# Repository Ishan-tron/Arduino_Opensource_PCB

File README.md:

# Arduino_Opensource_PCB
Arduino PCB Designs on KICAD

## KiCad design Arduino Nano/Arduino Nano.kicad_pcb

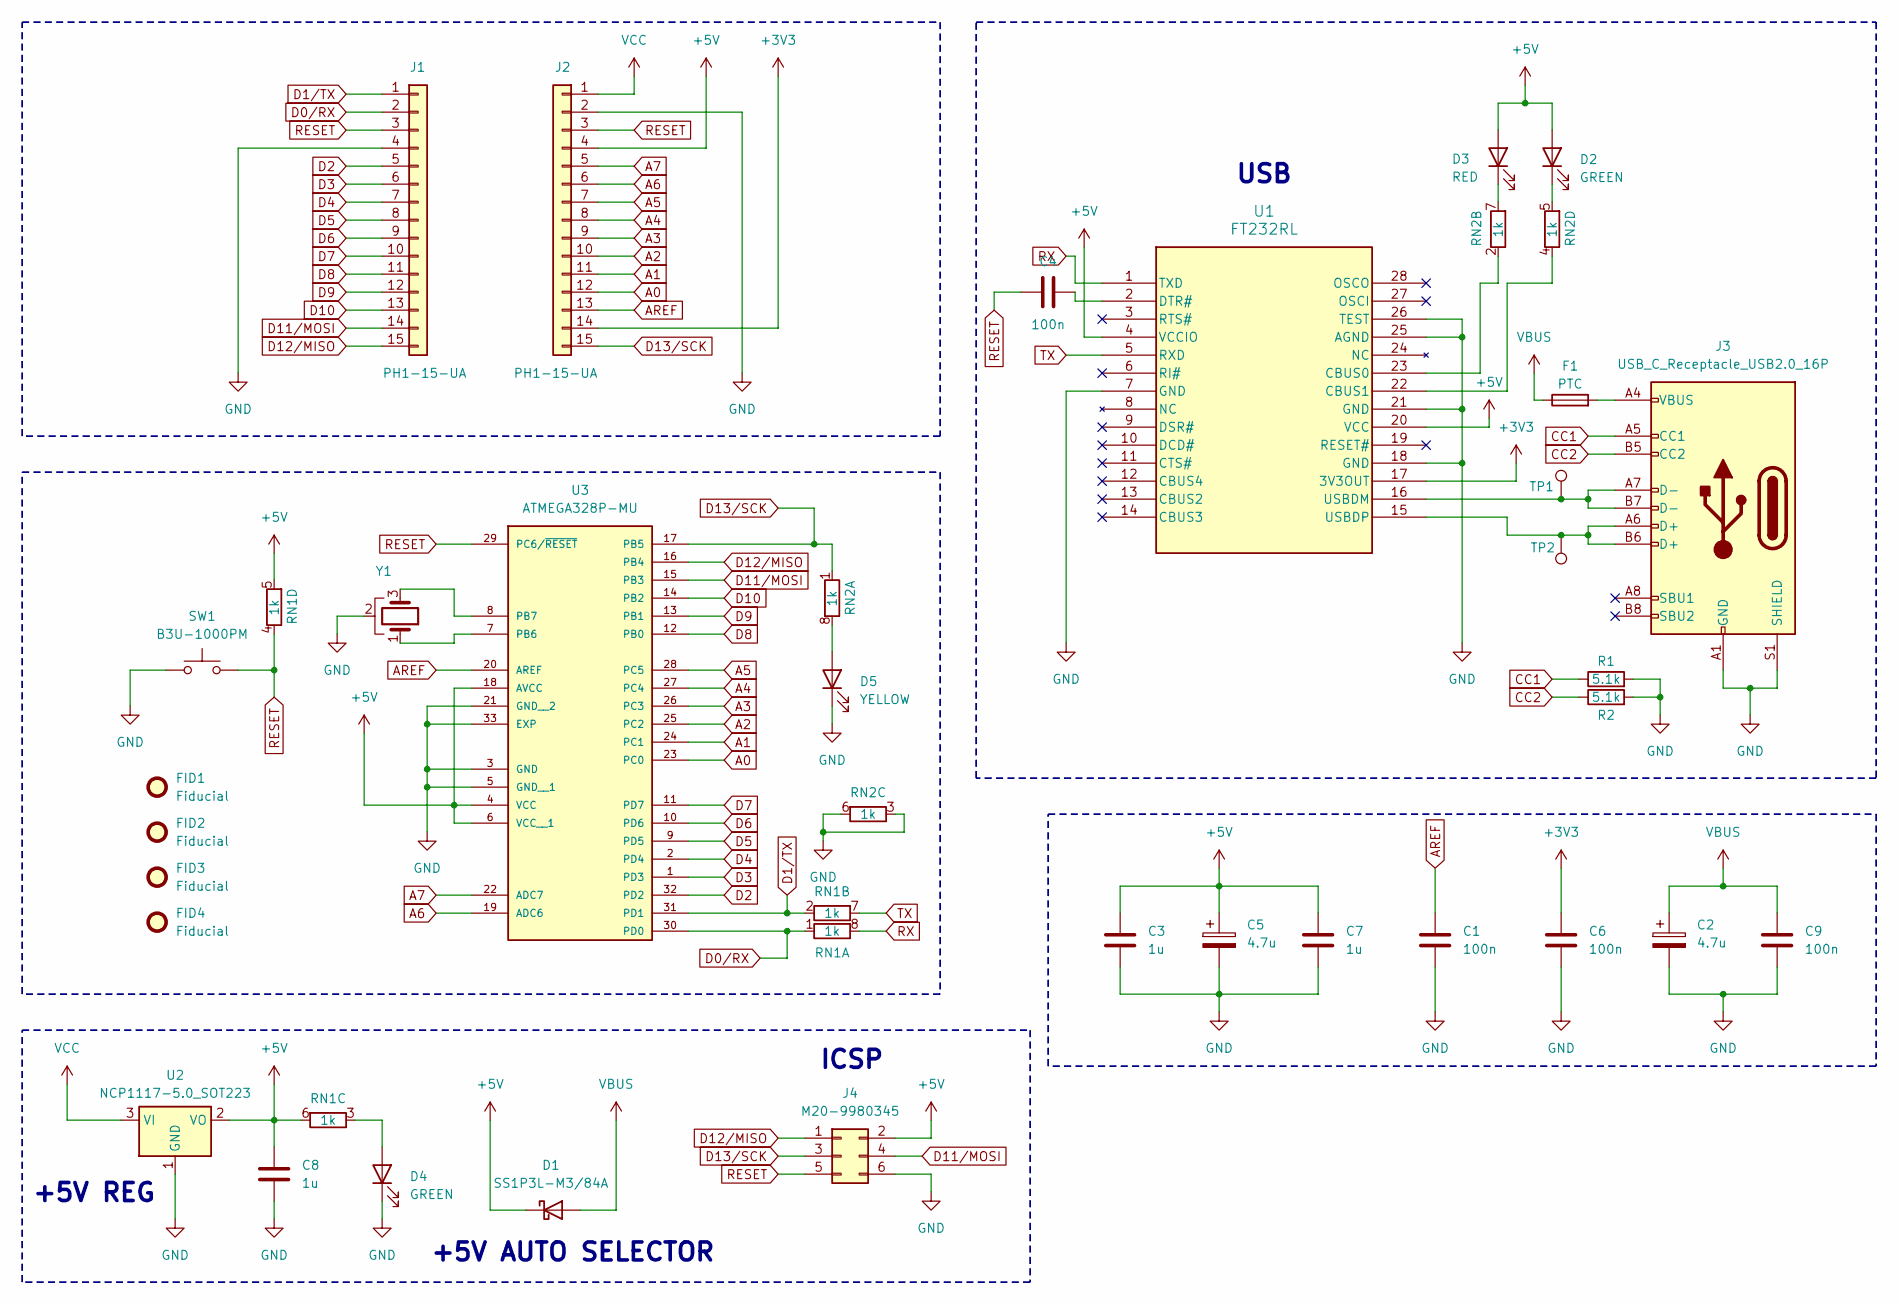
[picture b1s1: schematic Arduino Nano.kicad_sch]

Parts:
C1, C4, C6, C9: 100n; C_0603_1608Metric
C2, C5: 4.7u; CP_EIA-3216-10_Kemet-I
C3, C7, C8: 1u; C_0603_1608Metric
D1: SS1P3L-M3/84A; D_SMP_DO-220AA
D2, D4: GREEN; LED_0805_2012Metric
D3: RED; LED_0805_2012Metric
D5: YELLOW; LED_0805_2012Metric
F1: PTC; Fuse_0603_1608Metric
FID1, FID2, FID3, FID4: Fiducial; Fiducial_1mm_Mask2mm
J1, J2: PH1-15-UA; PinHeader_1x15_P2.54mm_Vertical
J3: USB_C_Receptacle_USB2.0_16P; USB_C_Receptacle_GCT_USB4110
J4: M20-9980345; PinHeader_2x03_P2.54mm_Vertical
R1, R2: 5.1k; R_0603_1608Metric
RN1, RN2: 1k; R_Array_Convex_4x0612
SW1: B3U-1000PM
TP1, TP2: TestPoint; TestPoint_Pad_D1.0mm
U1: FT232RL; SSOP-28_5.3x10.2mm_P0.65mm
U2: NCP1117-5.0_SOT223; SOT-223-3_TabPin2
U3: ATMEGA328P-MU; VQFN-32-1EP_5x5mm_P0.5mm_EP3.1x3.1mm
Y1: CSTNE16M0V530000R0; Resonator_SMD_Murata_CSTxExxV-3Pin_3.0x1.1mm

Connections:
+3V3: C6.2, J2.14, U1.17 (3V3OUT)
+5V: C3.1, C5.1, C7.1, C8.1, D1.1 (K), D2.2 (A), D3.2 (A), J2.4, J4.2, RN1.5 (R4.2), RN1.6 (R3.2), U1.4 (VCCIO), U1.20 (VCC), U2.2 (VO), U3.4 (VCC), U3.6 (VCC__1), U3.18 (AVCC)
A0: J2.12, U3.23 (PC0)
A1: J2.11, U3.24 (PC1)
A2: J2.10, U3.25 (PC2)
A3: J2.9, U3.26 (PC3)
A4: J2.8, U3.27 (PC4)
A5: J2.7, U3.28 (PC5)
A6: J2.6, U3.19 (ADC6)
A7: J2.5, U3.22 (ADC7)
AREF: C1.1, J2.13, U3.20 (AREF)
CC1: J3.A5 (CC1), R1.1
CC2: J3.B5 (CC2), R2.1
D0/RX: J1.2, RN1.1 (R1.1), U3.30 (PD0)
D1/TX: J1.1, RN1.2 (R2.1), U3.31 (PD1)
D2: J1.5, U3.32 (PD2)
D3: J1.6, U3.1 (PD3)
D4: J1.7, U3.2 (PD4)
D5: J1.8, U3.9 (PD5)
D6: J1.9, U3.10 (PD6)
D7: J1.10, U3.11 (PD7)
D8: J1.11, U3.12 (PB0)
D9: J1.12, U3.13 (PB1)
D10: J1.13, U3.14 (PB2)
D11/MOSI: J1.14, J4.4, U3.15 (PB3)
D12/MISO: J1.15, J4.1, U3.16 (PB4)
D13/SCK: J2.15, J4.3, RN2.1 (R1.1), U3.17 (PB5)
GND: C1.2, C2.2, C3.2, C5.2, C6.1, C7.2, C8.2, C9.2, D4.1 (K), D5.1 (K), J1.4, J2.2, J3.A1 (GND), J3.A12 (GND), J3.B1 (GND), J3.B12 (GND), J3.S1 (SHIELD), J4.6, R1.2, R2.2, RN2.3 (R3.1), RN2.6 (R3.2), SW1.1, U1.7 (GND), U1.18 (GND), U1.21 (GND), U1.25 (AGND), U1.26 (TEST), U2.1 (GND), U3.3 (GND), U3.5 (GND__1), U3.21 (GND__2), U3.33 (EXP), Y1.2
unnamed: D2.1 (K), RN2.5 (R4.2)
unnamed: D3.1 (K), RN2.7 (R2.2)
unnamed: D4.2 (A), RN1.3 (R3.1)
unnamed: D5.2 (A), RN2.8 (R1.2)
unnamed: F1.2, J3.A4 (VBUS), J3.A9 (VBUS), J3.B4 (VBUS), J3.B9 (VBUS)
unnamed: RN2.2 (R2.1), U1.23 (CBUS0)
unnamed: RN2.4 (R4.1), U1.22 (CBUS1)
unnamed: C4.2, U1.2 (DTR#)
unnamed: J3.A7 (D-), J3.B7 (D-), TP1.1, U1.16 (USBDM)
unnamed: J3.A6 (D+), J3.B6 (D+), TP2.1, U1.15 (USBDP)
unnamed: U3.7 (PB6), Y1.1
unnamed: U3.8 (PB7), Y1.3
RESET: C4.1, J1.3, J2.3, J4.5, RN1.4 (R4.1), SW1.2, U3.29 (PC6/~RESET)
RX: RN1.8 (R1.2), U1.1 (TXD)
TX: RN1.7 (R2.2), U1.5 (RXD)
VBUS: C2.1, C9.1, D1.2 (A), F1.1
VCC: J2.1, U2.3 (VI)

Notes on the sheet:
ICSP
USB
+5V AUTO SELECTOR
+5V REG

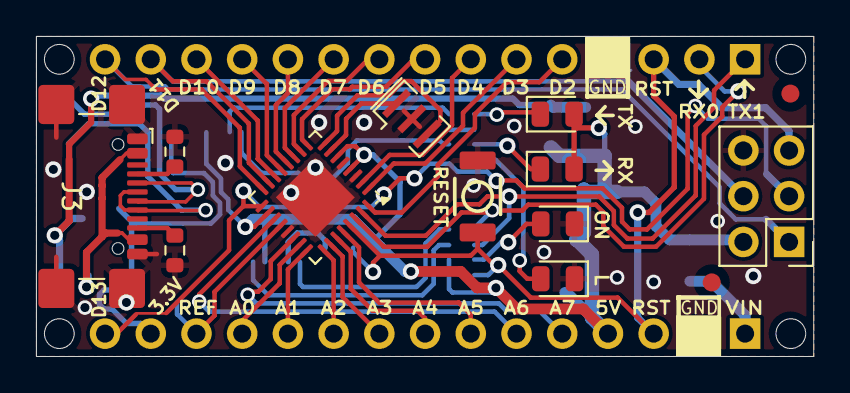
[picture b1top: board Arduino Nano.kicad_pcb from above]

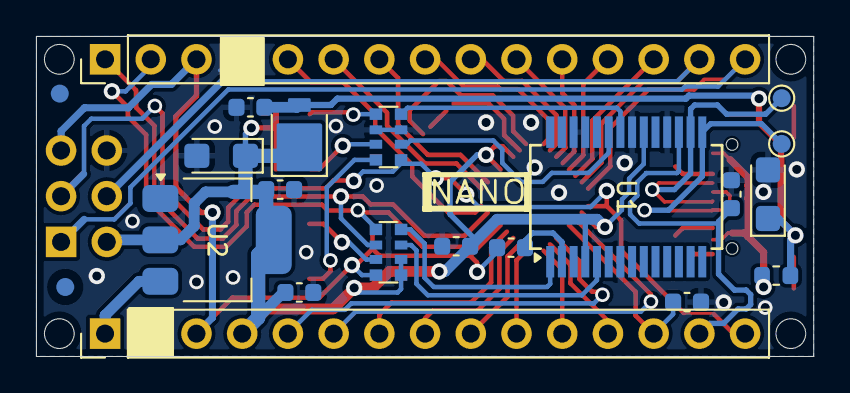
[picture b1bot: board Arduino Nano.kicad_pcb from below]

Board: 2 copper layers, 43.2 x 17.8 mm, 34 parts (21 on the bottom side), 45 nets.

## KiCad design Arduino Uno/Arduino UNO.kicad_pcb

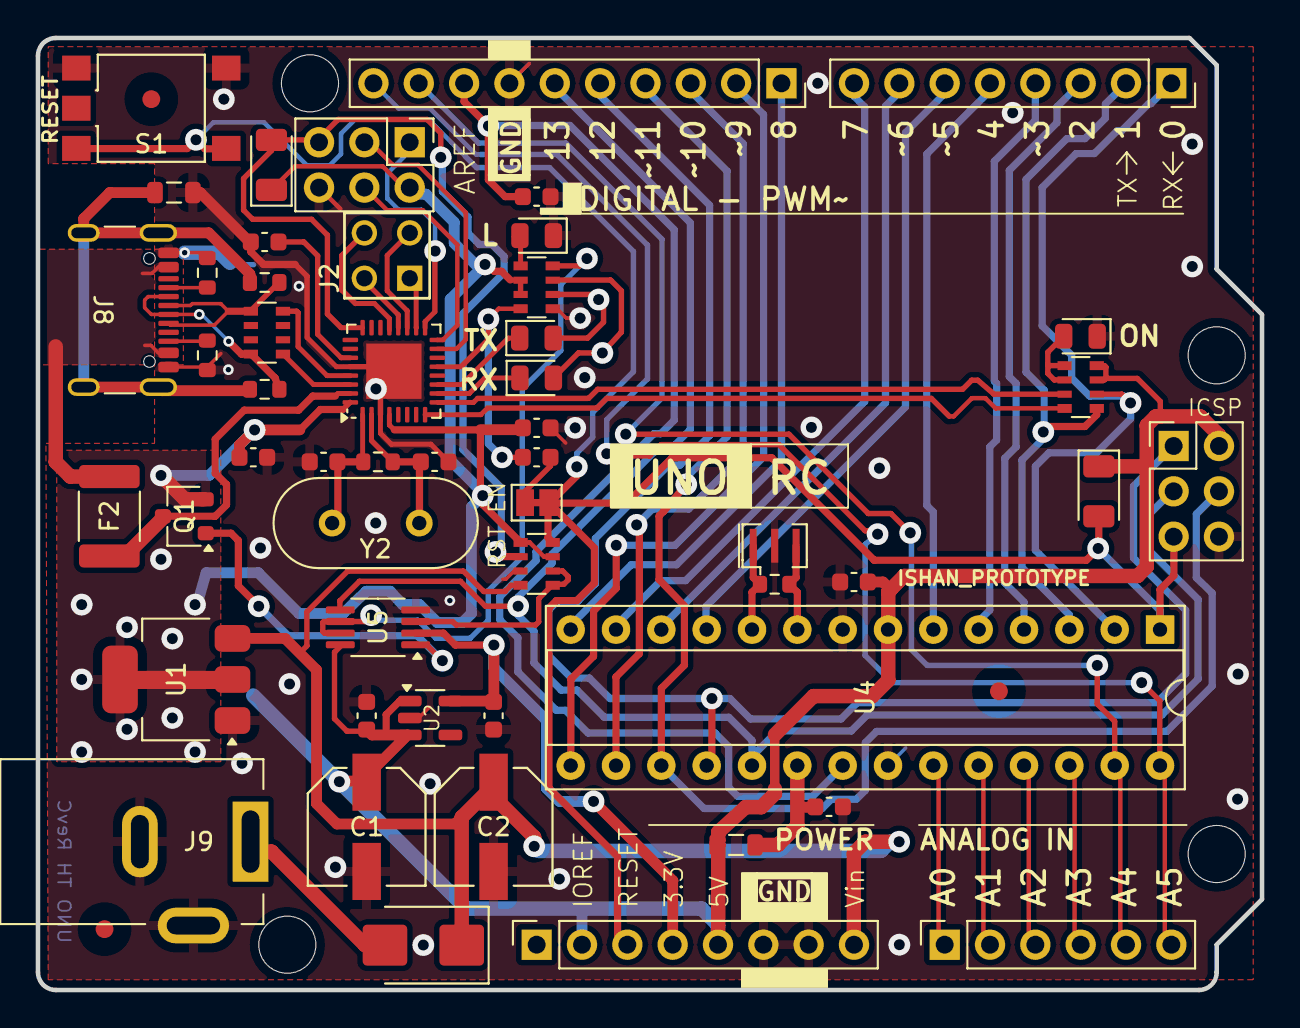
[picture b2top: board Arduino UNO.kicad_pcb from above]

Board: 2 copper layers, 68.6 x 53.3 mm, 56 parts (1 on the bottom side), 62 nets.

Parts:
C1, C2: 47u; CAP_EEHZA1E470P
C3, C4, C6, C7, C8, C9, C12: 100n; C_0603_1608Metric
C5, C10: 1u; C_0603_1608Metric
C11, C13: 22p; C_0603_1608Metric
D1: CGRB307-G; D_SMB
D2, D3: CD1206-S01575; D_1206_3216Metric
D4, D5, D6: YELLOW; LED_0805_2012Metric
D7: GREEN; LED_0805_2012Metric
F2: MF-MSMF050-2; Fuse_1812_4532Metric_Pad1.30x3.40mm_HandSolder
FB1: 1kΩ@100MHz; L_0805_2012Metric
FB2: 10uH; L_0805_2012Metric
FID1, FID2, FID3: Fiducial; Fiducial_1mm_Mask3mm
J1, J3: M20-9980345; PinHeader_2x03_P2.54mm_Vertical
J2: M20-9980245; CONN_M20-9980245_HRW
J4: PPTC101LFBN-RC; PinSocket_1x10_P2.54mm_Vertical
J5, J7: PPTC081LFBN-RC; PinSocket_1x08_P2.54mm_Vertical
J6: PPTC061LFBN-RC; PinSocket_1x06_P2.54mm_Vertical
J8: USB_C_Receptacle_USB2.0_16P; USB_C_Receptacle_GCT_USB4105-xx-A_16P_TopMnt_Horizontal
J9: PJ-102AH; BarrelJack_Kycon_KLDX-0202-xC_Horizontal
JP1, JP2: SolderJumper_2_Open; SolderJumper-2_P1.3mm_Open_Pad1.0x1.5mm
Q1: FDN340P; SC-59
R1, R2: 1M; R_0603_1608Metric
R3, R4: 5k1; R_0603_1608Metric
RN1: 10k; R_Array_Convex_4x0603
RN2, RN4: 1k; R_Array_Convex_4x0603
RN3: 22R; R_Array_Convex_4x0603
S1: TS06-667-30-BK-100-G-SMT-TR; SW_TS06-667-30-BK-100-G-SMT-TR
U1: NCP1117-5.0_SOT223; SOT-223-3_TabPin2
U2: LP2985-3.3; SOT-23-5
U3: ATMEGA16U2-MU; VQFN-32-1EP_5x5mm_P0.5mm_EP3.1x3.1mm
U4: ATMEGA328P-PU; DIP-28_W7.62mm_Socket
U5: LMV358IDGKR; MSOP-8_3x3mm_P0.65mm
Y1: CSTNE16M0V530000R0; Resonator_SMD_Murata_CSTxExxV-3Pin_3.0x1.1mm
Y2: LFXTAL003240BULK; Crystal_HC49-4H_Vertical
Z1, Z2: 5pF@1MHz; R_0603_1608Metric

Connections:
+3.3V: C5.2, J7.4, U2.5 (VOUT), U5.2
+5V: C1.1, C3.2, C4.1, C8.2, C9.1, D2.1 (K), D3.1 (K), FB2.1, J1.2, J3.2, J7.2, J7.5, Q1.2 (S), RN1.3 (R3.1), RN1.5 (R4.2), RN2.2 (R2.1), RN2.3 (R3.1), RN4.3 (R3.1), RN4.4 (R4.1), U1.2 (VO), U2.1 (VIN), U2.3 (ON/~OFF), U3.4 (VCC), U3.32 (AVCC), U4.7 (VCC), U5.8 (VCC+)
AD0: J6.1, U4.23 (PC0)
AD1: J6.2, U4.24 (PC1)
AD2: J6.3, U4.25 (PC2)
AD3: J6.4, U4.26 (PC3)
AD4/SDA: J4.9, J6.5, U4.27 (PC4)
AD5/SCL: J4.10, J6.6, U4.28 (PC5)
AREF: C6.1, J4.8, U4.21 (AREF)
AVCC: C12.1, FB2.2, U4.20 (AVCC)
CC1: J8.A5 (CC1), R3.1
CC2: J8.B5 (CC2), R4.1
CMP: RN1.1 (R1.1), RN1.2 (R2.1), U5.3
D+: J8.A6 (D+), J8.B6 (D+), RN3.5 (R4.2), Z1.1
D-: J8.A7 (D-), J8.B7 (D-), RN3.8 (R1.2), Z2.1
DTR: C7.1, RN2.4 (R4.1), U3.13 (PD7)
GATE_CMD: Q1.1 (G), U5.1
GND: C1.2, C2.2, C3.1, C4.2, C5.1, C6.2, C8.1, C9.2, C10.1, C11.2, C12.2, C13.2, D4.1 (K), D7.1 (K), FB1.2, J1.6, J3.6, J4.7, J7.6, J7.7, J8.A1 (GND), J8.A12 (GND), J8.B1 (GND), J8.B12 (GND), J9.2, J9.3, JP2.1 (A), JP2.2 (B), R3.2, R4.2, RN1.7 (R2.2), RN2.5 (R4.2), S1.1, S1.2, U1.1 (GND), U2.2 (GND), U3.3 (GND), U3.28 (UGND), U3.33 (EXP), U4.8 (GND), U4.22 (GND__1), U5.4 (GND), Y1.2
IO0: J5.1, RN4.2 (R2.1), U4.2 (PD0)
IO1: J5.2, RN4.1 (R1.1), U4.3 (PD1)
IO2: J5.3, U4.4 (PD2)
IO3: J5.4, U4.5 (PD3)
IO4: J5.5, U4.6 (PD4)
IO5: J5.6, U4.11 (PD5)
IO6: J5.7, U4.12 (PD6)
IO7: J5.8, U4.13 (PD7)
IO8: J4.1, U4.14 (PB0)
IO9: J4.2, U4.15 (PB1)
M8RXD: RN4.7 (R2.2), U3.9 (PD3)
M8TXD: RN4.8 (R1.2), U3.8 (PD2)
MISO: J3.1, J4.5, U4.18 (PB4)
MISO2: J1.1, U3.17 (PB3)
MOSI: J3.4, J4.4, U4.17 (PB3)
MOSI2: J1.4, U3.16 (PB2)
unnamed: D1.2 (A), J9.1
unnamed: D4.2 (A), RN2.1 (R1.1)
unnamed: D5.2 (A), RN2.6 (R3.2)
unnamed: D6.2 (A), RN2.7 (R2.2)
unnamed: D7.2 (A), RN4.5 (R4.2), RN4.6 (R3.2)
unnamed: RN2.8 (R1.2), U5.6, U5.7
unnamed: C13.1, R1.1, U3.2 (PC0), Y2.1
unnamed: C10.2, U3.27 (UCAP)
unnamed: C11.1, R1.2, U3.1 (XTAL1), Y2.2
unnamed: R2.2, U4.9 (PB6), Y1.3
unnamed: R2.1, U4.10 (PB7), Y1.1
PB4: J2.1, U3.18 (PB4)
PB5: J2.3, U3.19 (PB5)
PB6: J2.2, U3.20 (PB6)
PB7: J2.4, U3.21 (PB7)
RD+: RN3.4 (R4.1), U3.29 (D+)
RD-: RN3.1 (R1.1), U3.30 (D-)
RESET: C7.2, D2.2 (A), J3.5, J7.3, JP1.1 (A), JP1.2 (B), RN1.4 (R4.1), S1.3, S1.4, U4.1 (PC6/~RESET)
RESET2: D3.2 (A), J1.5, RN1.6 (R3.2), U3.24 (PC1//~RESET)
RXLED: D6.1 (K), U3.10 (PD4)
SCK: J3.3, J4.6, U4.19 (PB5), U5.5
SCK2: J1.3, U3.15 (PB1)
SS: J4.3, U4.16 (PB2)
TXLED: D5.1 (K), U3.11 (PD5)
USBVCC: F2.2, Q1.3 (D), U3.31 (UVCC)
USHIELD: FB1.1, J8.S1 (SHIELD), Z1.2, Z2.2
VCC: C2.1, D1.1 (K), J7.8, RN1.8 (R1.2), U1.3 (VI)
XUSB: F2.1, J8.A4 (VBUS), J8.A9 (VBUS), J8.B4 (VBUS), J8.B9 (VBUS)

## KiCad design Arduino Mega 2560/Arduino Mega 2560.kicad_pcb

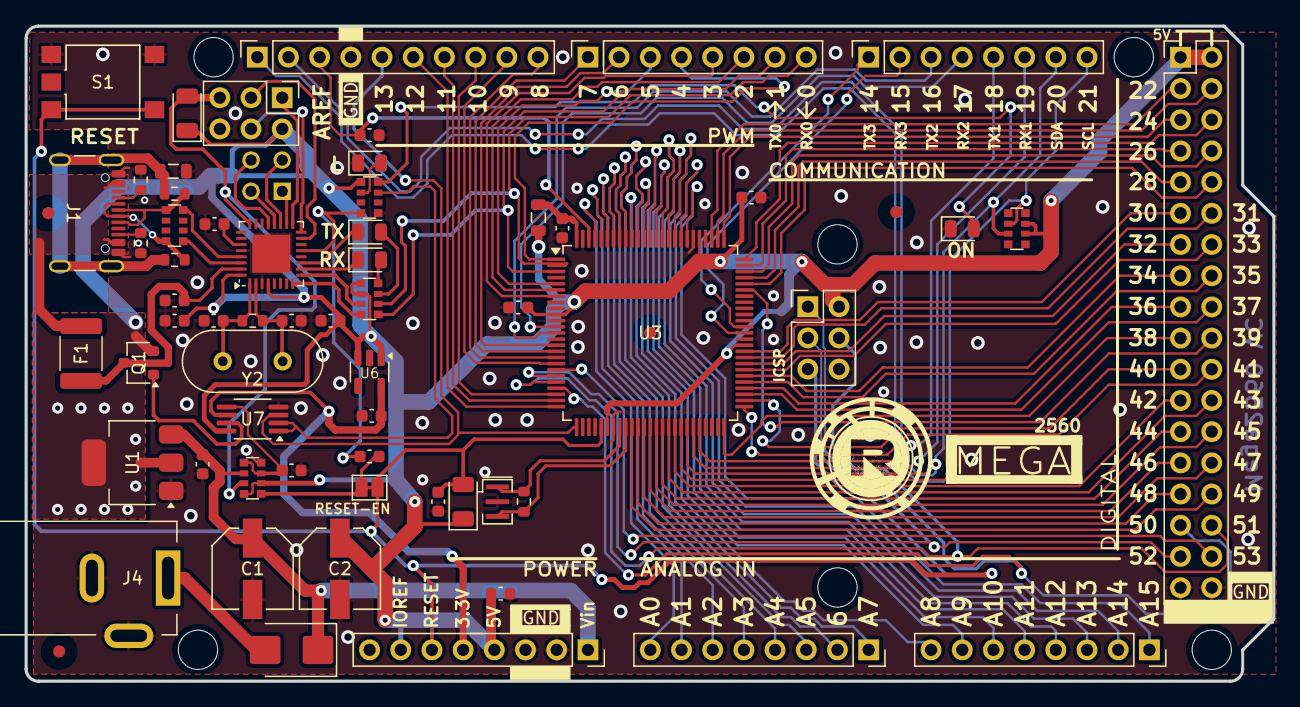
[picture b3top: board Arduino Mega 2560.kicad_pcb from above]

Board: 2 copper layers, 101.6 x 53.3 mm, 66 parts (1 on the bottom side), 112 nets.

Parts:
C1, C2: 47u; CAP_EEHZA1E470P
C3, C4, C5, C6, C7, C8, C9, C10, C11, C13, C14, C18: 100n; C_0603_1608Metric
C12, C15: 1u; C_0603_1608Metric
C16, C17: 22p; C_0603_1608Metric
D1, D2, D5: YELLOW; LED_0805_2012Metric
D3, D7: CD1206-S01575; D_1206_3216Metric
D4: CGRB307-G; D_SMB
D6: GREEN; LED_0805_2012Metric
F1: MF-MSMF050-2; Fuse_1812_4532Metric_Pad1.30x3.40mm_HandSolder
FB1, FB2: 1kΩ@100MHz; L_0805_2012Metric
FID1, FID2, FID3, FID4: Fiducial; Fiducial_1mm_Mask3mm
J1: USB_C_Receptacle_USB2.0_16P; USB_C_Receptacle_GCT_USB4105-xx-A_16P_TopMnt_Horizontal
J2, J12: M20-9980345; PinHeader_2x03_P2.54mm_Vertical
J3: M20-9980245; CONN_M20-9980245_HRW
J4: PJ-102AH; BarrelJack_Kycon_KLDX-0202-xC_Horizontal
J5: PPTC182LFBN-RC
J6: PPTC101LFBN-RC; PinSocket_1x10_P2.54mm_Vertical
J7, J8, J9, J10, J11: PPTC081LFBN-RC; PinSocket_1x08_P2.54mm_Vertical
JP1, JP2: SolderJumper_2_Open; SolderJumper-2_P1.3mm_Open_Pad1.0x1.5mm
Q1: PMV48XP; SC-59
R1, R2: 1M; R_0603_1608Metric
R3, R4: 5k1; R_0603_1608Metric
RN1, RN5: 10k; R_Array_Convex_4x0612
RN2: 22R; R_Array_Convex_4x0612
RN3, RN4: 1k; R_Array_Convex_4x0612
RV1, RV2: 5pF@1MHz; R_0603_1608Metric
S1: TS06-667-30-BK-100-G-SMT-TR; SW_TS06-667-30-BK-100-G-SMT-TR
U1: NCP1117-5.0_SOT223; SOT-223-3_TabPin2
U3: ATMEGA2560-16AU; TQFP-100_14x14mm_P0.5mm
U4: ATMEGA16U2-MU; VQFN-32-1EP_5x5mm_P0.5mm_EP3.1x3.1mm
U6: LP2985-3.3; SOT-23-5
U7: LMV358IDGKR; MSOP-8_3x3mm_P0.65mm
Y1: CSTNE16M0V530000R0; Resonator_SMD_Murata_CSTxExxV-3Pin_3.0x1.1mm
Y2: LFXTAL003240BULK; Crystal_HC49-4H_Vertical

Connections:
8PB4: J3.1, U4.18 (PB4)
8PB5: J3.3, U4.19 (PB5)
8PB6: J3.2, U4.20 (PB6)
8PB7: J3.4, U4.21 (PB7)
+3.3V: C15.2, J11.5, U6.5 (VOUT), U7.6
+5V: C2.1, C6.1, C7.1, C8.1, C11.1, C13.2, D3.1 (K), D7.1 (K), FB2.2, J2.2, J5.1, J5.2, J11.4, J11.7, J12.2, Q1.2 (S), RN1.6 (R3.2), RN1.7 (R2.2), RN3.1 (R1.1), RN4.5 (R4.2), RN4.6 (R3.2), RN5.2 (R2.1), RN5.8 (R1.2), U1.2 (VO), U3.10 (VCC), U3.31 (VCC1), U3.61 (VCC2), U3.80 (VCC3), U4.4 (VCC), U4.32 (AVCC), U6.1 (VIN), U6.3 (ON/~OFF), U7.8 (VCC+)
ADC0: J10.8, U3.97 ((ADC0)PF0)
ADC1: J10.7, U3.96 ((ADC1)PF1)
ADC2: J10.6, U3.95 ((ADC2)PF2)
ADC3: J10.5, U3.94 ((ADC3)PF3)
ADC4: J10.4, U3.93 ((ADC4/TCK)PF4)
ADC5: J10.3, U3.92 ((ADC5/TMS)PF5)
ADC6: J10.2, U3.91 ((ADC6/TDO)PF6)
ADC7: J10.1, U3.90 ((ADC7/TDI)PF7)
ADC8: J9.8, U3.89 (PK0(ADC8/PCINT16))
ADC9: J9.7, U3.88 (PK1(ADC9/PCINT17))
ADC10: J9.6, U3.87 (PK2(ADC10/PCINT18))
ADC11: J9.5, U3.86 (PK3(ADC11/PCINT19))
ADC12: J9.4, U3.85 (PK4(ADC12/PCINT20))
ADC13: J9.3, U3.84 (PK5(ADC13/PCINT21))
ADC14: J9.2, U3.83 (PK6(ADC14/PCINT22))
ADC15: J9.1, U3.82 (PK7(ADC15/PCINT23))
AREF: C5.1, J6.3, U3.98 (AREF)
AVCC: C18.1, FB2.1, U3.100 (AVCC)
CC1: J1.A5 (CC1), R3.2
CC2: J1.B5 (CC2), R4.2
CMP: C14.2, RN5.3 (R3.1), RN5.5 (R4.2), U7.5
D+: J1.A6 (D+), J1.B6 (D+), RN2.5 (R4.2), RV2.2
D-: J1.A7 (D-), J1.B7 (D-), RN2.8 (R1.2), RV1.2
DTR: C9.1, RN3.4 (R4.1), U4.13 (PD7)
GATE_CMD: Q1.1 (G), U7.7
GND: C1.2, C2.2, C3.2, C4.2, C5.2, C6.2, C7.2, C8.2, C10.2, C11.2, C12.2, C13.1, C14.1, C15.1, C16.2, C17.2, C18.2, D5.1 (K), D6.1 (K), FB1.1, J1.A1 (GND), J1.A12 (GND), J1.B1 (GND), J1.B12 (GND), J2.6, J4.2, J4.3, J5.35, J5.36, J6.4, J11.2, J11.3, J12.6, JP1.1 (A), JP1.2 (B), R3.1, R4.1, RN3.5 (R4.2), RN5.4 (R4.1), S1.1, S1.2, U1.1 (GND), U3.11 (GND), U3.32 (GND1), U3.62 (GND2), U3.81 (GND3), U3.99 (AGND), U4.3 (GND), U4.28 (UGND), U4.33 (EXP), U6.2 (GND), U7.4 (GND), Y1.2
L13: RN3.7 (R2.2), U7.1, U7.2
M8RXD: RN4.7 (R2.2), U4.9 (PD3)
M8TXD: RN4.8 (R1.2), U4.8 (PD2)
MISO2: J2.1, U4.17 (PB3)
MOSI2: J2.4, U4.16 (PB2)
unnamed: D1.2 (A), RN4.3 (R3.1)
unnamed: D2.2 (A), RN4.4 (R4.1)
unnamed: D4.2 (A), J4.1
unnamed: D5.2 (A), RN3.2 (R2.1)
unnamed: D6.2 (A), RN3.8 (R1.2)
unnamed: C17.1, R2.2, U4.2 (PC0), Y2.1
unnamed: C12.1, U4.27 (UCAP)
unnamed: C16.1, R2.1, U4.1 (XTAL1), Y2.2
PA0: J5.3, U3.78 ((AD0)PA0)
PA1: J5.4, U3.77 ((AD1)PA1)
PA2: J5.5, U3.76 ((AD2)PA2)
PA3: J5.6, U3.75 ((AD3)PA3)
PA4: J5.7, U3.74 ((AD4)PA4)
PA5: J5.8, U3.73 ((AD5)PA5)
PA6: J5.9, U3.72 ((AD6)PA6)
PA7: J5.10, U3.71 ((AD7)PA7)
PB0: J5.34, U3.19 ((SS/PCINT0)PB0)
PB1: J5.33, J12.3, U3.20 ((SCK/PCINT1)PB1)
PB2: J5.32, J12.4, U3.21 ((MOSI/PCINT2)PB2)
PB3: J5.31, J12.1, U3.22 ((MISO/PCINT3)PB3)
PB4: J6.8, U3.23 ((OC2A/PCINT4)PB4)
PB5: J6.7, U3.24 ((OC1A/PCINT5)PB5)
PB6: J6.6, U3.25 ((OC1B/PCINT6)PB6)
PB7: J6.5, U3.26 ((OC0A/OC1C/PCINT7)PB7), U7.3
PC0: J5.18, U3.53 ((A8)PC0)
PC1: J5.17, U3.54 ((A9)PC1)
PC2: J5.16, U3.55 ((A10)PC2)
PC3: J5.15, U3.56 ((A11)PC3)
PC4: J5.14, U3.57 ((A12)PC4)
PC5: J5.13, U3.58 ((A13)PC5)
PC6: J5.12, U3.59 ((A14)PC6)
PC7: J5.11, U3.60 ((A15)PC7)
PD7: J5.19, U3.50 ((T0)PD7)
PE0: J7.8, RN4.2 (R2.1), U3.2 ((RXD0/PCIN8)PE0)
PE1: J7.7, RN4.1 (R1.1), U3.3 ((TXD0)PE1)
PE3: J7.3, U3.5 ((OC3A/AIN1)PE3)
PE4: J7.6, U3.6 ((OC3B/INT4)PE4)
PE5: J7.5, U3.7 ((OC3C/INT5)PE5)
PG0: J5.22, U3.51 ((WR)PG0)
PG1: J5.21, U3.52 ((RD)PG1)
PG2: J5.20, U3.70 ((ALE)PG2)
PG5: J7.4, U3.1 ((OC0B)PG5)
PH3: J7.2, U3.15 (PH3(OC4A))
PH4: J7.1, U3.16 (PH4(OC4B))
PH5: J6.10, U3.17 (PH5(OC4C))
PH6: J6.9, U3.18 (PH6(OC2B))
PL0: J5.30, U3.35 (PL0(ICP4))
PL1: J5.29, U3.36 (PL1(ICP5))
PL2: J5.28, U3.37 (PL2(T5))
PL3: J5.27, U3.38 (PL3(OC5A))
PL4: J5.26, U3.39 (PL4(OC5B))
PL5: J5.25, U3.40 (PL5(OC5C))
PL6: J5.24, U3.41 (PL6)
PL7: J5.23, U3.42 (PL7)
RD+: RN2.4 (R4.1), U4.29 (D+)
RD-: RN2.1 (R1.1), U4.30 (D-)
RESET: C3.1, C9.2, D7.2 (A), J11.6, J12.5, JP2.1 (A), JP2.2 (B), RN5.1 (R1.1), S1.3, S1.4, U3.30 (RESET)
RESET2: D3.2 (A), J2.5, RN5.7 (R2.2), U4.24 (PC1//~RESET)
RXD1: J8.6, U3.45 ((RXD1/INT2)PD2)
RXD2: J8.4, U3.12 (PH0(RXD2))
RXD3: J8.2, U3.63 (PJ0(RXD3/PCINT9))
RXL: D2.1 (K), U4.10 (PD4)
SCK2: J2.3, U4.15 (PB1)
SCL: J6.1, J8.8, RN1.2 (R2.1), U3.43 ((SCL/INT0)PD0)
SDA: J6.2, J8.7, RN1.3 (R3.1), U3.44 ((SDA/INT1)PD1)
TXD1: J8.5, U3.46 ((TXD1/INT3)PD3)
TXD2: J8.3, U3.13 (PH1(TXD2))
TXD3: J8.1, U3.64 (PJ1(TXD3/PCINT10))
TXL: D1.1 (K), U4.11 (PD5)
USBVCC: C10.1, F1.1, Q1.3 (D), U4.31 (UVCC)
USHIELD: FB1.2, J1.S1 (SHIELD), RV1.1, RV2.1
VCC: C1.1, C4.1, D4.1 (K), J11.1, RN5.6 (R3.2), U1.3 (VI)
XTAL1: R1.1, U3.34 (XTAL1), Y1.3
XTAL2: R1.2, U3.33 (XTAL2), Y1.1
XVCC: F1.2, J1.A4 (VBUS), J1.A9 (VBUS), J1.B4 (VBUS), J1.B9 (VBUS)
